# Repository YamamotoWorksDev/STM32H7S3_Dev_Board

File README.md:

# STM32H7S3 Development Board (rev.C)
This board is a development board featuring the STM32H7S3Z8T MCU.

## How to buy
- [Tindie(International)](https://www.tindie.com/products/41582/)
- [BASE(Japan)](https://miyworks.base.shop/items/135242611)

## Specifications
- MCU specs.
  - STMicroelectronics [STM32H7S3Z8T](https://www.st.com/en/microcontrollers-microprocessors/stm32h7s3z8.html)(Arm Cortex-M7 Core/600MHz max)
  - External Crystal Oscilator(24MHz)
  - External FLASH(256Mbits OctoSPI)
  - USB type-C(USB2.0 High-Speed supported)
  - [UF2 bootloader](https://github.com/yamamo2shun1/JUMBLEQ/tree/main/STM32CubeIDE/MX25UW25645GXDI00_STM32H7S3Z8T)

- DSP specs.
  - Analog Devices [ADAU1466](https://www.analog.com/en/products/adau1466.html)(SigmaDSP Core/294.912MHz max)

## Pinout

## Size

## Byte Options

## Application Example
- [JUMBLEQ](https://github.com/yamamo2shun1/JUMBLEQ)

## Photo

## License
The hardware design files in this repository are licensed under the
**CERN Open Hardware Licence Version 2 - Permissive (CERN-OHL-P-2.0)**.

Unless otherwise stated, the following are treated as hardware design files covered by CERN-OHL-P-2.0:

- KiCad schematic files
- PCB layout files

A copy of the license text is provided in the `LICENSE` file.

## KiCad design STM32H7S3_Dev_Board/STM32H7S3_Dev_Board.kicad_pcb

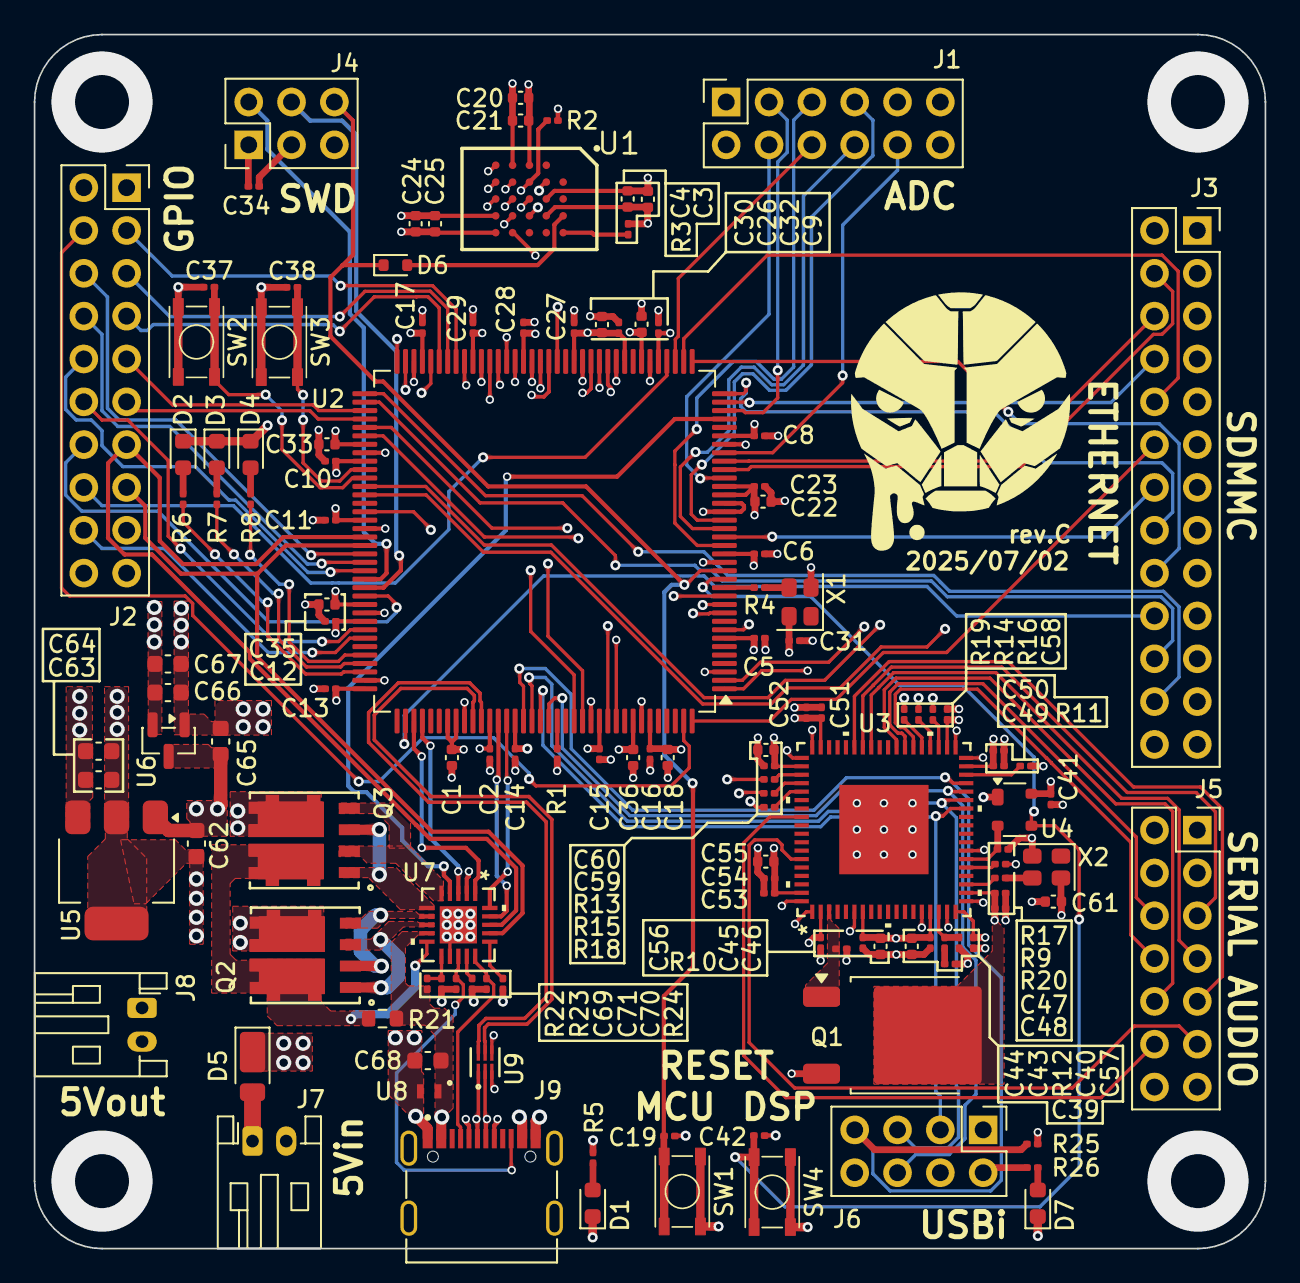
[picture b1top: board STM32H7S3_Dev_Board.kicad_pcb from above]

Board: 6 copper layers, 73.0 x 72.0 mm, 130 parts (0 on the bottom side), 135 nets.

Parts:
C1, C22: 1uF; C_0402_1005Metric
C2, C5, C6, C8, C9, C10, C11, C12, C13, C14, C15, C16, C17, C19, C23, C26, C27, C28, C29, C31, C34, C37, C38, C41, C42, C43, C45, C48, C50, C52, C54, C56, C57, C58, C59, C71: 100nF; C_0201_0603Metric
C3, C18, C20, C24, C30: 4.7uF; C_0402_1005Metric
C4, C21, C25, C61: 100nF; C_0402_1005Metric
C32, C33, C35, C36: 2.2uF; C_0402_1005Metric
C39: 5.6nF; C_0201_0603Metric
C40: 150pF; C_0201_0603Metric
C44, C46, C55, C60: 10uF; C_0402_1005Metric
C47, C49, C51, C53: 10nF; C_0201_0603Metric
C62, C63, C64: 4.7uF; C_0603_1608Metric
C65, C66, C67: 1uF; C_0603_1608Metric
C68: 2.2uF/50V; C_0603_1608Metric
C69, C70: 560pF; C_0201_0603Metric
D1, D2, D3, D4, D7: LED; LED_0603_1608Metric
D5: D_Schottky; D_PowerDI-123
D6: D_Schottky; D_SOD-523
J1: Conn_02x06_Odd_Even; PinSocket_2x06_P2.54mm_Vertical
J2: Conn_02x10_Odd_Even; PinSocket_2x10_P2.54mm_Vertical
J3: Conn_02x13_Odd_Even; PinSocket_2x13_P2.54mm_Vertical
J4: 15910060; PinHeader_2x03_P2.54mm_Vertical
J5: Conn_02x07_Odd_Even; PinSocket_2x07_P2.54mm_Vertical
J6: Conn_02x04_Odd_Even; PinHeader_2x04_P2.54mm_Vertical
J7, J8: Conn_01x02; JST_PH_S2B-PH-K_1x02_P2.00mm_Horizontal
J9: UB1611-HGN; Gangyuan_UB1611-HGN
Q1: STD2805T4; TO-252-2
Q2, Q3: STL40DN3LLH5; SON_DN3LLH5_STM
R1, R2, R3, R11, R22, R24, R25: 10k; R_0201_0603Metric
R4, R9, R13, R14, R15, R16, R18, R19, R20: 33R; R_0201_0603Metric
R5, R6, R7, R8, R10, R26: 1k; R_0201_0603Metric
R12: 4.32k; R_0201_0603Metric
R17: 100k; R_0201_0603Metric
R21: 22mR; R_0603_1608Metric
R23: 2k4; R_0201_0603Metric
SW1, SW2, SW3, SW4: SKRPABE010
U1: MX25UW25645GXDI00; BGA24C100P5X5_800X600X120
U2: STM32H7S3Z8Tx; LQFP-144_20x20mm_P0.5mm
U3: ADAU1466WBCPZ300RL; CP_72_6_ADI
U4: ADM811TARTZ; SOT-143
U5: AP7361EA-33E-13; SOT-223-3_TabPin2
U6: AP2127N-1.8TRG1; SOT-23
U7: TCPP03-M20; QFN-20L_4.0X4.0X0.75_STM
U8: ESDA25P35-1U1M; QFN1610_STM
U9: ECMF2-40A100N6; QFN6L_ECMF2_STM
X1: 24MHz; Oscillator_SMD_SeikoEpson_SG210-4Pin_2.5x2.0mm
X2: 12.288MHz; Oscillator_SMD_SeikoEpson_SG210-4Pin_2.5x2.0mm

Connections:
1V8: C3.2, C4.2, C20.2, C21.2, C24.2, C25.2, C26.2, C27.2, C28.2, C29.2, C30.2, C66.1, C67.1, R2.2, R3.1, U1.B4 (VCC), U1.D1 (VCCQ), U1.E4 (VCCQ), U2.45 (VDDXSPI1), U2.51 (VDDXSPI1), U2.57 (VDDXSPI1), U2.63 (VDDXSPI1), U6.2 (VO)
3V3: C1.2, C5.2, C6.2, C8.2, C9.2, C10.2, C11.2, C12.2, C13.2, C14.2, C15.2, C16.2, C17.2, C18.2, C22.2, C23.2, C31.2, C34.2, C39.2, C40.1, C41.1, C43.1, C44.1, C45.1, C46.1, C56.1, C57.1, C58.1, C59.1, C60.1, C61.2, C63.1, C64.1, J1.1, J1.2, J2.1, J2.2, J3.1, J3.2, J4.1, J5.1, J5.2, Q1.3 (E), R5.1, R10.1, R25.2, U2.3 (VBAT), U2.7 (VDD), U2.17 (VDD), U2.24 (VREFP), U2.25 (VDDA), U2.31 (VDD), U2.41 (VDD), U2.69 (VDD), U2.81 (VDD), U2.88 (VDD), U2.100 (VDD), U2.108 (VDD), U2.115 (VDD50USB), U2.116 (VDD33USB), U2.123 (VDD), U2.133 (VDD), U2.139 (VDD), U3.2 (IOVDD), U3.7 (AVDD), U3.15 (PVDD), U3.18 (IOVDD), U3.38 (IOVDD), U3.56 (IOVDD), U4.4 (VCC), U5.3 (VO), U7.2 (VCC_VCONN), X1.4 (Vcc), X2.4 (Vcc)
5V: D5.1 (K), Q3.5 (D1), Q3.6 (D1)
5V_UCPD: C62.1, C65.1, J8.1, Q2.5 (D1), Q2.6 (D1), U5.1 (VI), U6.3 (VI)
/DSP/BCLK_OUT1: J5.6, U3.43 (BCLK_OUT1)
/DSP/BCLK_OUT2: J5.5, U3.48 (BCLK_OUT2)
/DSP/CLKOUT: J5.3, J5.4, R9.2, U2.87 (PC9)
/DSP/DSP_BCLK_IN0: R13.1, U2.72 (PD13)
/DSP/DSP_BCLK_OUT0: R14.1, U2.11 (PE5)
/DSP/DSP_LRCLK_IN0: R15.1, U2.71 (PD12)
/DSP/DSP_LRCLK_OUT0: R16.1, U2.10 (PE4)
/DSP/DSP_RESET: C42.1, SW4.1, SW4.2, U2.14 (PH1), U4.3 (~MR)
/DSP/DSP_SDATA_IN0: R18.1, U2.68 (PD11)
/DSP/DSP_SDATA_OUT0: R19.1, U2.12 (PE6)
/DSP/LRCLK_OUT1: J5.8, U3.42 (LRCLK_OUT1/MP5)
/DSP/LRCLK_OUT2: J5.7, U3.47 (LRCLK_OUT2/MP8)
/DSP/MCLK: R20.2, U3.21 (XTALIN/MCLK)
/DSP/SDATA_IN1: J5.12, U3.62 (SDATA_IN1)
/DSP/SDATA_IN2: J5.11, U3.67 (SDATA_IN2)
/DSP/SDATA_OUT1: J5.10, U3.44 (SDATA_OUT1)
/DSP/SDATA_OUT2: J5.9, U3.49 (SDATA_OUT2)
/DSP/USBi_MISO: J6.3, U2.126 (PM14), U3.30 (MISO/SDA)
/DSP/USBi_MOSI: J6.6, U2.127 (PM13), U3.32 (MOSI/ADDR1)
/DSP/USBi_SCLK: J6.5, U2.125 (PM11), U3.31 (SCLKC/SCL)
/DSP/USBi_SS: J6.7, R25.1, U2.124 (PM12), U3.33 (SS/ADDR0)
/DSP/~RESET: R17.2, U3.24 (RESET*), U4.2 (~RESET)
/MCU/ADC1_IN0: J1.4, U2.26 (PA0)
/MCU/ADC1_IN3: J1.3, U2.34 (PA6)
/MCU/ADC1_IN5: J1.6, U2.39 (PB1)
/MCU/ADC1_IN10: J1.5, U2.18 (PC0)
/MCU/ADC1_IN12: J1.8, U2.20 (PC2)
/MCU/ADC1_IN13: J1.7, U2.21 (PC3)
/MCU/ADC1_IN15: J1.10, U2.29 (PA3)
/MCU/DEBUG_SWCLK: J4.4, U2.96 (PA14(JTCK)
/MCU/DEBUG_SWDIO: J4.2, U2.95 (PA13(JTMS)
/MCU/ETH_MDC: J3.14, U2.19 (PC1)
/MCU/ETH_MDIO: J3.6, U2.28 (PA2)
/MCU/ETH_MII_RX_ER: J3.24, U2.73 (PB10)
/MCU/ETH_RMII_CRS_DV: J3.8, U2.35 (PA7)
/MCU/ETH_RMII_INTN: J3.20, U2.110 (PD4)
/MCU/ETH_RMII_REF_CLK: J3.4, U2.27 (PA1)
/MCU/ETH_RMII_RXD0: J3.16, U2.36 (PC4)
/MCU/ETH_RMII_RXD1: J3.18, U2.37 (PC5)
/MCU/ETH_RMII_TXD0: J3.10, U2.38 (PB0)
/MCU/ETH_RMII_TXD1: J3.12, U2.144 (PB7)
/MCU/ETH_RMII_TX_EN: J3.22, U2.74 (PB11)
/MCU/FDCAN2_RX: J2.9, U2.75 (PB12)
/MCU/FDCAN2_TX: J2.11, U2.76 (PB13)
/MCU/I2C2_SCL: J2.13, U2.90 (PA8), U7.18 (SCL)
/MCU/I2C2_SDA: J2.15, U2.91 (PA9), U7.17 (SDA)
/MCU/I2S3_CK: J2.12, U2.101 (PC10)
/MCU/I2S3_SDI: J2.18, U2.102 (PC11)
/MCU/I2S3_SDO: J2.16, U2.40 (PB2)
/MCU/I2S3_WS: J2.14, U2.97 (PA15(JTDI))
/MCU/LED0: R6.1, U2.106 (PD2)
/MCU/LED1: R7.1, U2.105 (PD1)
/MCU/LED2: R8.1, U2.104 (PD0)
/MCU/LPUART1_CTS: J2.8, U2.93 (PA11)
/MCU/LPUART1_RTS: J2.10, U2.94 (PA12)
/MCU/LPUART1_RX: J2.6, U2.92 (PA10)
/MCU/LPUART1_TX: J2.4, U2.143 (PB6)
/MCU/NRST: C19.2, D6.1 (K), J4.6, SW1.3 (K), SW1.4 (A), U2.15 (NRST)
/MCU/OSPI_CS: R2.1, U1.C2 (CS), U2.64 (PO0)
/MCU/OSPI_DQS: U1.C3 (DQS), U2.59 (PO2)
/MCU/OSPI_SCLK: U1.B2 (SCLK), U2.53 (PO4)
/MCU/OSPI_SIO0: U1.D3 (SIO0), U2.55 (PP0)
/MCU/OSPI_SIO1: U1.D2 (SIO1), U2.61 (PP1)
/MCU/OSPI_SIO2: U1.C4 (SIO2), U2.48 (PP2)
/MCU/OSPI_SIO3: U1.D4 (SIO3), U2.49 (PP3)
/MCU/OSPI_SIO4: U1.D5 (SIO4), U2.47 (PP4)
/MCU/OSPI_SIO5: U1.E3 (SIO5), U2.54 (PP5)
/MCU/OSPI_SIO6: U1.E2 (SIO6), U2.58 (PP6)
/MCU/OSPI_SIO7: U1.E1 (SIO7), U2.60 (PP7)
/MCU/SDMMC2_CK: J3.3, U2.130 (PD6)
/MCU/SDMMC2_CMD: J3.5, U2.131 (PD7)
/MCU/SDMMC2_D0: J3.7, U2.77 (PB14)
/MCU/SDMMC2_D1: J3.9, U2.78 (PB15)
/MCU/SDMMC2_D2: J3.11, U2.134 (PB3(JTDO)
/MCU/SDMMC2_D3: J3.13, U2.135 (PB4(NJTRST))
/MCU/SDMMC2_D4: J3.15, U2.1 (PB8)
/MCU/SDMMC2_D5: J3.17, U2.2 (PB9)
/MCU/SDMMC2_D6: J3.19, U2.84 (PC6)
/MCU/SDMMC2_D7: J3.21, U2.85 (PC7)
/MCU/UCPD_CC1: U2.111 (PM0), U7.1 (CC1)
/MCU/UCPD_CC2: U2.112 (PM1), U7.3 (CC2)
/MCU/UCPD_INT: U2.121 (PM8), U7.19 (FLG_n)
/MCU/UCPD_ISENSE: U2.33 (PA5), U7.4 (I_ANA)
/MCU/UCPD_PWR_EN: U2.122 (PM9), U7.20 (EN)
/MCU/USART3_CK: J2.7, U2.67 (PD10)
/MCU/USART3_RX: J2.5, U2.66 (PD9)
/MCU/USART3_TX: J2.3, U2.65 (PD8)
/MCU/USB_HS_D+: U2.119 (PM6), U9.6 (D+_ic)
/MCU/USB_HS_D-: U2.118 (PM5), U9.5 (D-_ic)
/MCU/USER_SW1: C37.2, SW2.3 (K), SW2.4 (A), U2.83 (PD15)
/MCU/USER_SW2: C38.2, SW3.3 (K), SW3.4 (A), U2.82 (PD14)
/USB/CC1: C70.1, J9.A5 (CC1), U7.15 (CC_1c)
/USB/CC2: C69.1, J9.B5 (CC2), U7.13 (CC_2c)
/USB/D+: J9.A6 (DP1), J9.B6 (DP2), U9.1 (D+_con)
/USB/D-: J9.A7 (DN1), J9.B7 (DN2), U9.2 (D-_con)
DVDD: C47.1, C48.1, C49.1, C50.1, C51.1, C52.1, C53.1, C54.1, C55.1, Q1.2 (C), U3.20 (DVDD), U3.35 (DVDD), U3.53 (DVDD), U3.71 (DVDD)
GND: C1.1, C2.1, C3.1, C4.1, C5.1, C6.1, C8.1, C9.1, C10.1, C11.1, C12.1, C13.1, C14.1, C15.1, C16.1, C17.1, C18.1, C19.1, C20.1, C21.1, C22.1, C23.1, C24.1, C25.1, C26.1, C27.1, C28.1, C29.1, C30.1, C31.1, C32.1, C33.1, C34.1, C35.1, C36.1, C37.1, C38.1, C41.2, C42.2, C43.2, C44.2, C45.2, C46.2, C47.2, C48.2, C49.2, C50.2, C51.2, C52.2, C53.2, C54.2, C55.2, C56.2, C57.2, C58.2, C59.2, C60.2, C61.1, C62.2, C63.2, C64.2, C65.2, C66.2, C67.2, C68.2, C69.2, C70.2, C71.2, D1.1 (K), D2.1 (K), D3.1 (K), D4.1 (K), D7.1 (K), J1.9, J1.11, J1.12, J2.17, J2.19, J2.20, J3.23, J3.25, J3.26, J4.3, J4.5, J5.13, J5.14, J6.8, J7.2, J8.2, J9.A1_B12 (GND), J9.B1_A12 (GND), J9.S1 (SHIELD), J9.S2 (SHIELD), J9.S3 (SHIELD), J9.S4 (SHIELD), R1.1, R11.1, R17.1, R23.2, R24.2, SW1.1, SW1.2, SW2.1, SW2.2, SW3.1, SW3.2, SW4.3 (K), SW4.4 (A), U1.B3 (GND), U1.C1 (VSSQ), U1.E5 (VSSQ), U2.8 (VSS), U2.16 (VSS), U2.22 (VSSA), U2.23 (VREFM), U2.30 (VSS), U2.42 (VSS), U2.46 (VSS), U2.50 (VSS), U2.56 (VSS), U2.62 (VSS), U2.70 (VSS), U2.80 (VSS), U2.89 (VSS), U2.99 (VSS), U2.107 (VSS), U2.117 (VSSUSB), U2.132 (VSS), U2.138 (VSS), U3.1 (DGND), U3.6 (AGND), U3.14 (PGND), U3.17 (DGND), U3.19 (DGND), U3.25 (DGND), U3.36 (DGND), U3.37 (DGND), U3.54 (DGND), U3.55 (DGND), U3.72 (DGND), U3.73 (EP(GND)), U4.1 (GND), U5.2 (GND), U6.1 (GND), U7.12 (GND), U7.21 (GND), U8.2, U9.3 (GND), U9.4 (GND), X1.2 (GND), X2.2 (GND)
MCU_DVDD: C2.2, C32.2, C33.2, C35.2, C36.2, U2.43 (VCAP1), U2.79 (VCAP2), U2.98 (VCAP3), U2.120 (DVDD), U2.137 (VCAP4)
unnamed: C39.1, R12.1
unnamed: D1.2 (A), R5.2
unnamed: D2.2 (A), R6.2
unnamed: D3.2 (A), R7.2
unnamed: D4.2 (A), R8.2
unnamed: D5.2 (A), J7.1
unnamed: D6.2 (A), U1.A4 (RESET)
unnamed: D7.2 (A), R26.2
unnamed: J6.2, R26.1
unnamed: Q1.1 (B), R10.2, U3.3 (VDRIVE)
unnamed: Q2.2 (G2), Q2.4 (G1), U7.7 (GDC_g)
unnamed: Q2.1 (S2), Q2.3 (S1), U7.8 (GDC_s)
unnamed: Q3.2 (G2), Q3.4 (G1), U7.5 (GDP_g)
unnamed: Q3.1 (S2), Q3.3 (S1), U7.6 (GDP_s)
unnamed: R3.2, U1.A5 (ECS)
unnamed: R1.2, U2.128 (BOOT0)
unnamed: R4.2, U2.13 (PH0)
unnamed: R13.2, U3.57 (BCLK_IN0)
unnamed: R14.2, U3.40 (BCLK_OUT0)
unnamed: R9.1, U3.23 (CLKOUT)
unnamed: R15.2, U3.58 (LRCLK_IN0/MP10)
unnamed: R16.2, U3.39 (LRCLK_OUT0/MP4)
unnamed: C40.2, R12.2, U3.16 (PLLFILT)
unnamed: R18.2, U3.59 (SDATA_IN0)
unnamed: R19.2, U3.41 (SDATA_OUT0)
unnamed: R11.2, U3.34 (SELFBOOT)
unnamed: C71.1, U7.14 (C_BIAS)
unnamed: R24.1, U7.16 (I2C_ADD)
unnamed: Q2.7 (D2), Q2.8 (D2), Q3.7 (D2), Q3.8 (D2), R21.1, U7.10 (I_SENSE)
unnamed: R22.2, R23.1, U7.11 (V_SENSE)
unnamed: R4.1, X1.3 (OUT)
unnamed: R20.1, X2.3 (OUT)
VBUS: C68.1, J9.A4_B9 (VBUS), J9.B4_A9 (VBUS), R21.2, R22.1, U7.9 (VBUS_c), U8.1

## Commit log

2026-03-09 Add .gitignore for KiCad
    Ignores KiCad temporary files, backups, and build artifacts to keep the repository clean.
2026-03-09 Add CERN Open Hardware Licence
    Adds the CERN-OHL-P v2 (Permissive) license to the repository to define the terms for use, modification, and distribution of the hardware design.
2026-03-09 Update .gitignore for STM32H7S3 Dev Board backups
    Ignores backup directories for the STM32H7S3 development board subprojects to keep the repository clean.
2026-03-09 Add KiCad project files.
2026-03-09 Update README with board details and specifications
    Added detailed information about the STM32H7S3 development board, including specifications, purchasing information, pinout, size, and licensing.
2026-03-09 Update README title for clarity and versioning
2026-03-09 Add Byte Options section to README
    Added Byte Options section with images to README.
2026-03-09 Add Rev C schematic PDF
    Adds the PDF version of the STM32H7S3 development board revision C schematic for easy reference.
2026-03-09 Add photos to README
    Added images to the README for visual reference.
2026-03-10 Enhance README with links in specifications
    Updated specifications section to include hyperlinks for STM32H7S3Z8T and ADAU1466.
2026-03-10 Update section headers in README.md for consistency
2026-03-12 Change the 3D model data path settings.
2026-03-17 Fix formatting in README links section
2026-03-25 Add application example section to README
